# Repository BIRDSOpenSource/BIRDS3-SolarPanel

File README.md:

<div align="center">
  
</div>

# BIRDS3-SolarPanel
 Documentation for the Solar Panel Boards used in the BIRDS3 Satellite

## About the BIRDS3 Program:

The project was led by Kyushu Institute of Technology in Japan and involves students from Sri Lanka, Bhutan, Nepal and Japan.
Satellite Names: NepaliSat-1 (Nepal), Raavana-1 (Sri Lanka) and Ugiusu (Japan)

Stakeholders: Nepal Academy of Science and Technology (NAST) for Nepal, Arthur C Clarke Institute for Modern Technologies (ACCIMT) for Sri Lanka, and Kyushu Institute of Technology (Kyutech) for Japan.

Project duration: 2018-2020

CubeSat: 1U (10x10x10) cm3

Weight: 1.13kg

Launch Date: 17th April 2019

BIRDS-3 has 4 main missions in total; LoRa Demonstration Mission (LDM), Imaging Mission (CAM), Attitude Determination and Control Mission (ADCS) and Software Configurable Backplane Mission (BPB) 

## Organisation structure

## Features

## I like this project, can I help you?
You are welcome 🙂

* Give us a star ⭐
* Watch repository to be notified about updates 👀
* If you will find some errors, report them in Issues 🐞
* Try Birds designs on some real computer and let us know how it worked in Discussions. 💬
* We would greatly appreciate if you would also tell others about this ecosystem, it helps us to improve BIRDS Open Source. Thank you!

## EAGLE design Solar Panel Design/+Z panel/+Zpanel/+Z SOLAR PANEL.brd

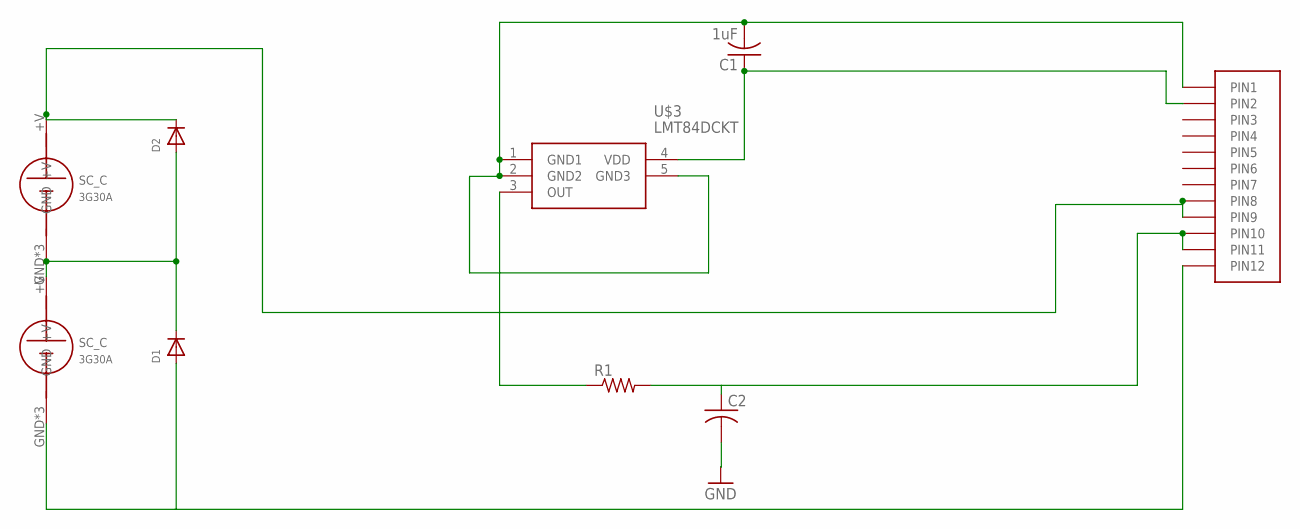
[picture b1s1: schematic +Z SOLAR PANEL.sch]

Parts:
C1: 1uF; C2012
C2: C-USC2012; C2012
D1, D2: DIODE_SOD-123FL; SOD-123FL
R1: R-US_R0402; R0402
U$1: HEADER12PIN
U$3: LMT84DCKT; SOT65P210X110-5N
U$4, U$5: SC_C

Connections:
+V: D2.C, U$1.P8 (PIN8), U$1.P9 (PIN9), U$4.+V
+VB: D1.C, D2.A, U$4.GND, U$4.GND1 (GND), U$4.GND2 (GND), U$5.+V
GND: C1.2, C2.2, D1.A, U$1.P1 (PIN1), U$1.P12 (PIN12), U$3.1 (GND1), U$3.2 (GND2), U$3.5 (GND3), U$5.GND, U$5.GND1 (GND), U$5.GND2 (GND)
unnamed: C1.1, U$1.P2 (PIN2), U$3.4 (VDD)
unnamed: R1.1, U$3.3 (OUT)
unnamed: C2.1, R1.2, U$1.P10 (PIN10), U$1.P11 (PIN11)

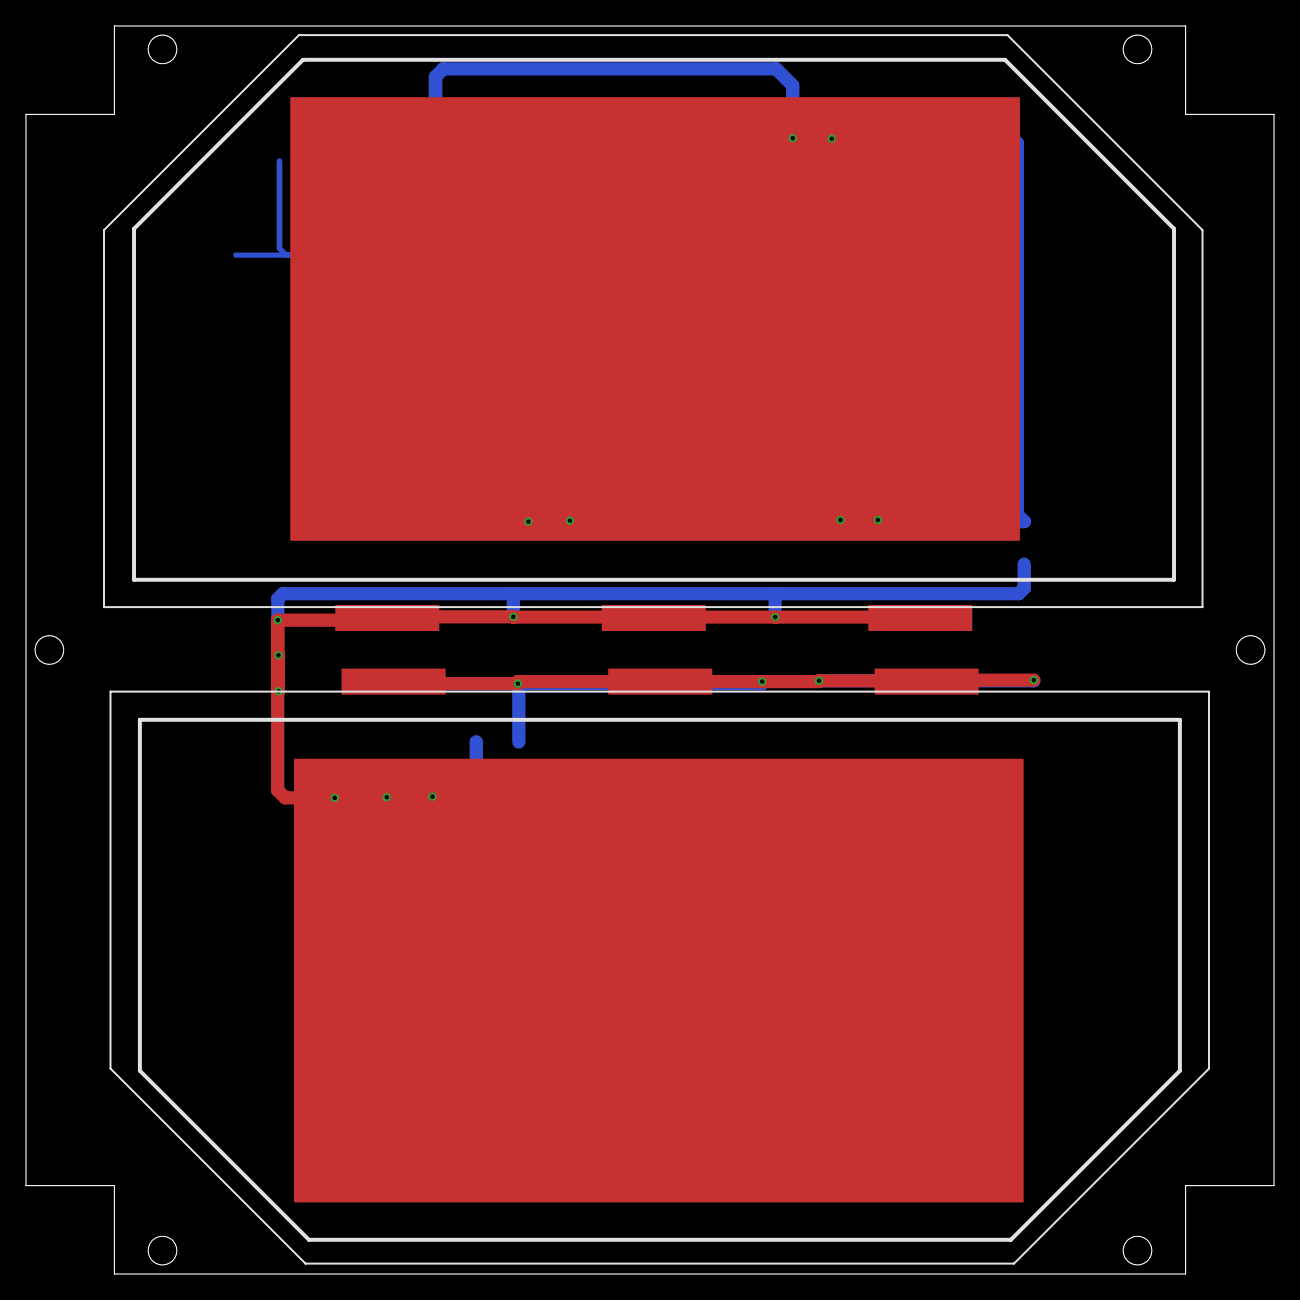
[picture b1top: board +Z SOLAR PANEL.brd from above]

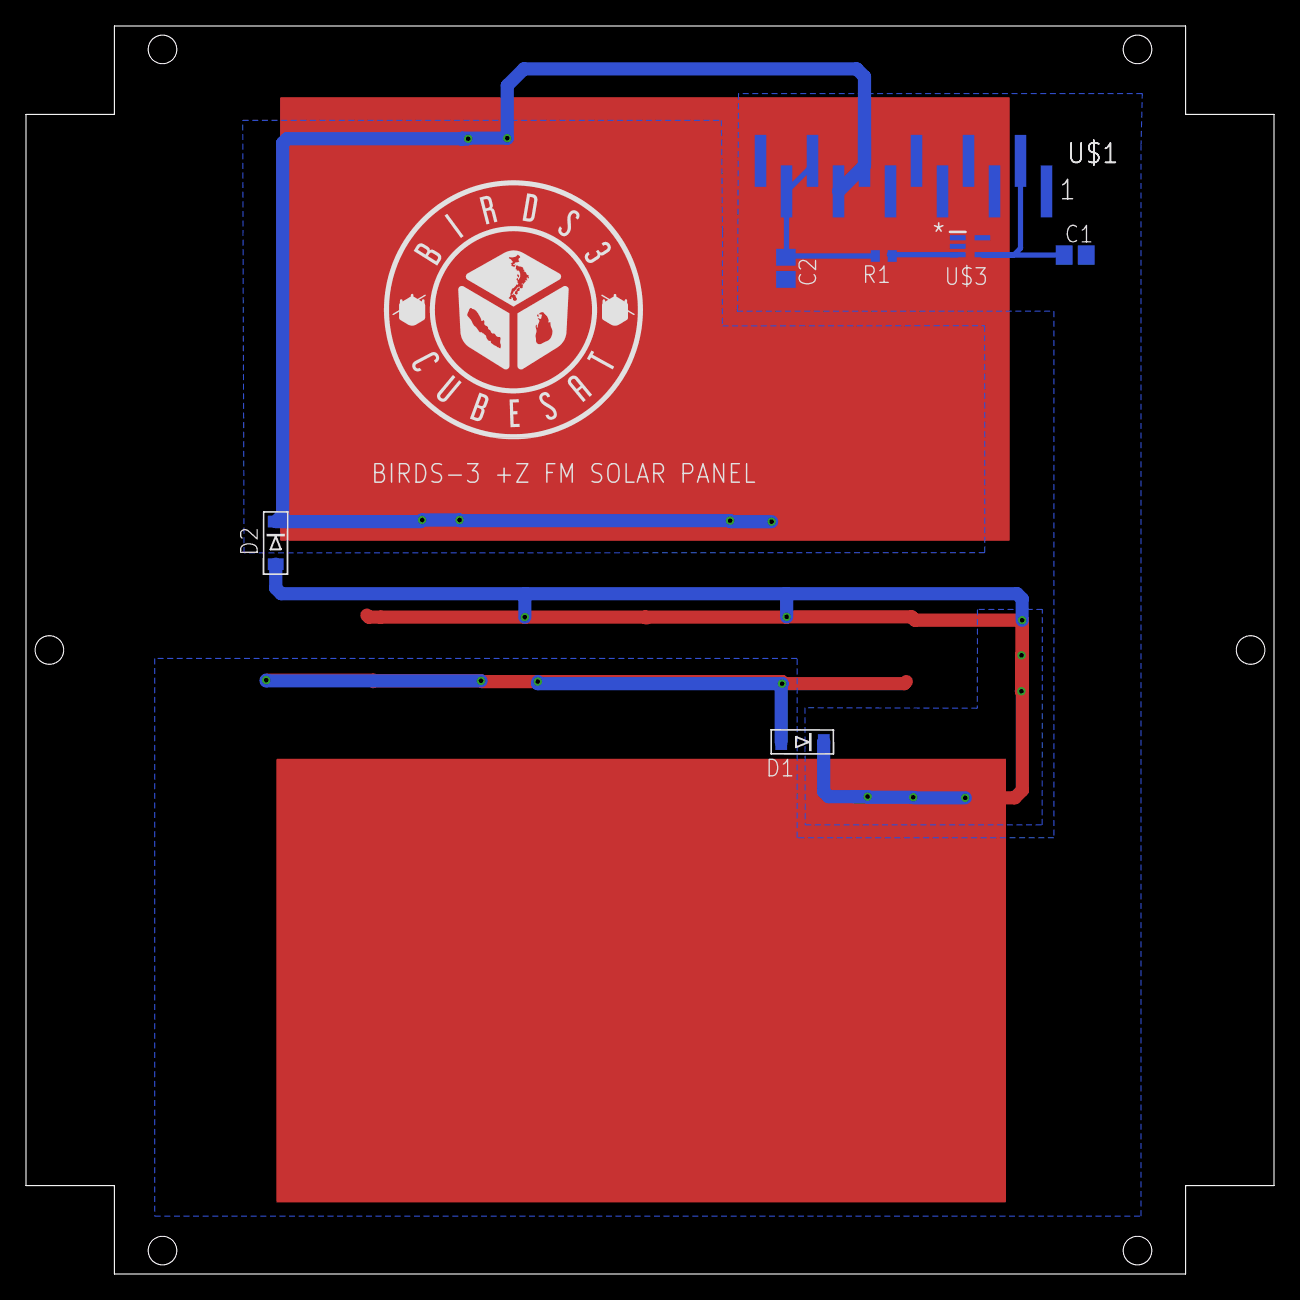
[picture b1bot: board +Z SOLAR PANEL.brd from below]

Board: 2 copper layers, 96.0 x 96.0 mm, 9 parts (5 on the bottom side), 6 nets.

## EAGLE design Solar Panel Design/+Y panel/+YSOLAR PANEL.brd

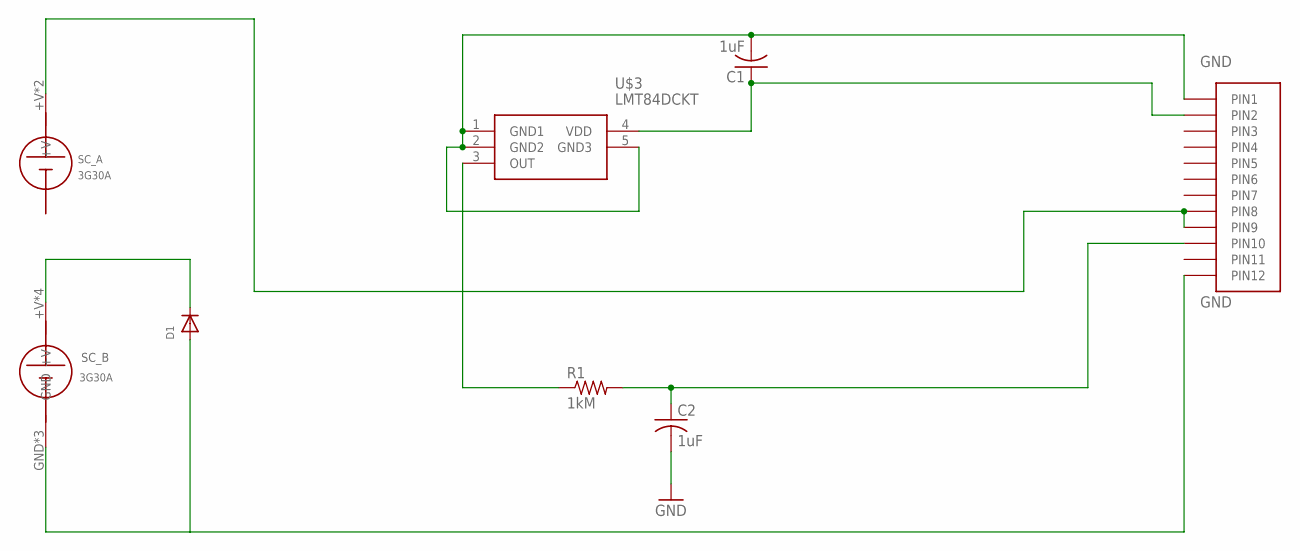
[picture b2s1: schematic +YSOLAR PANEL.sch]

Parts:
C1, C2: 1uF; C0805
D1: DIODE_SOD-123FL; SOD-123FL
R1: 1kM; R0402
SOLARCELL_A: SC_A
SOLARCELL_B: SC_B
U$1: HEADER12PIN
U$3: LMT84DCKT; SOT65P210X110-5N

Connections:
+V: SOLARCELL_A.+V, SOLARCELL_A.+V1, U$1.P8 (PIN8), U$1.P9 (PIN9)
+VB: D1.C, SOLARCELL_B.+V, SOLARCELL_B.+V2 (+V), SOLARCELL_B.+V3 (+V), SOLARCELL_B.+V4 (+V)
GND: C1.2, C2.2, D1.A, SOLARCELL_B.GND, SOLARCELL_B.GND1 (GND), SOLARCELL_B.GND2 (GND), U$1.P1 (PIN1), U$1.P12 (PIN12), U$3.1 (GND1), U$3.2 (GND2), U$3.5 (GND3)
unnamed: C1.1, U$1.P2 (PIN2), U$3.4 (VDD)
unnamed: R1.1, U$3.3 (OUT)
unnamed: C2.1, R1.2, U$1.P10 (PIN10)

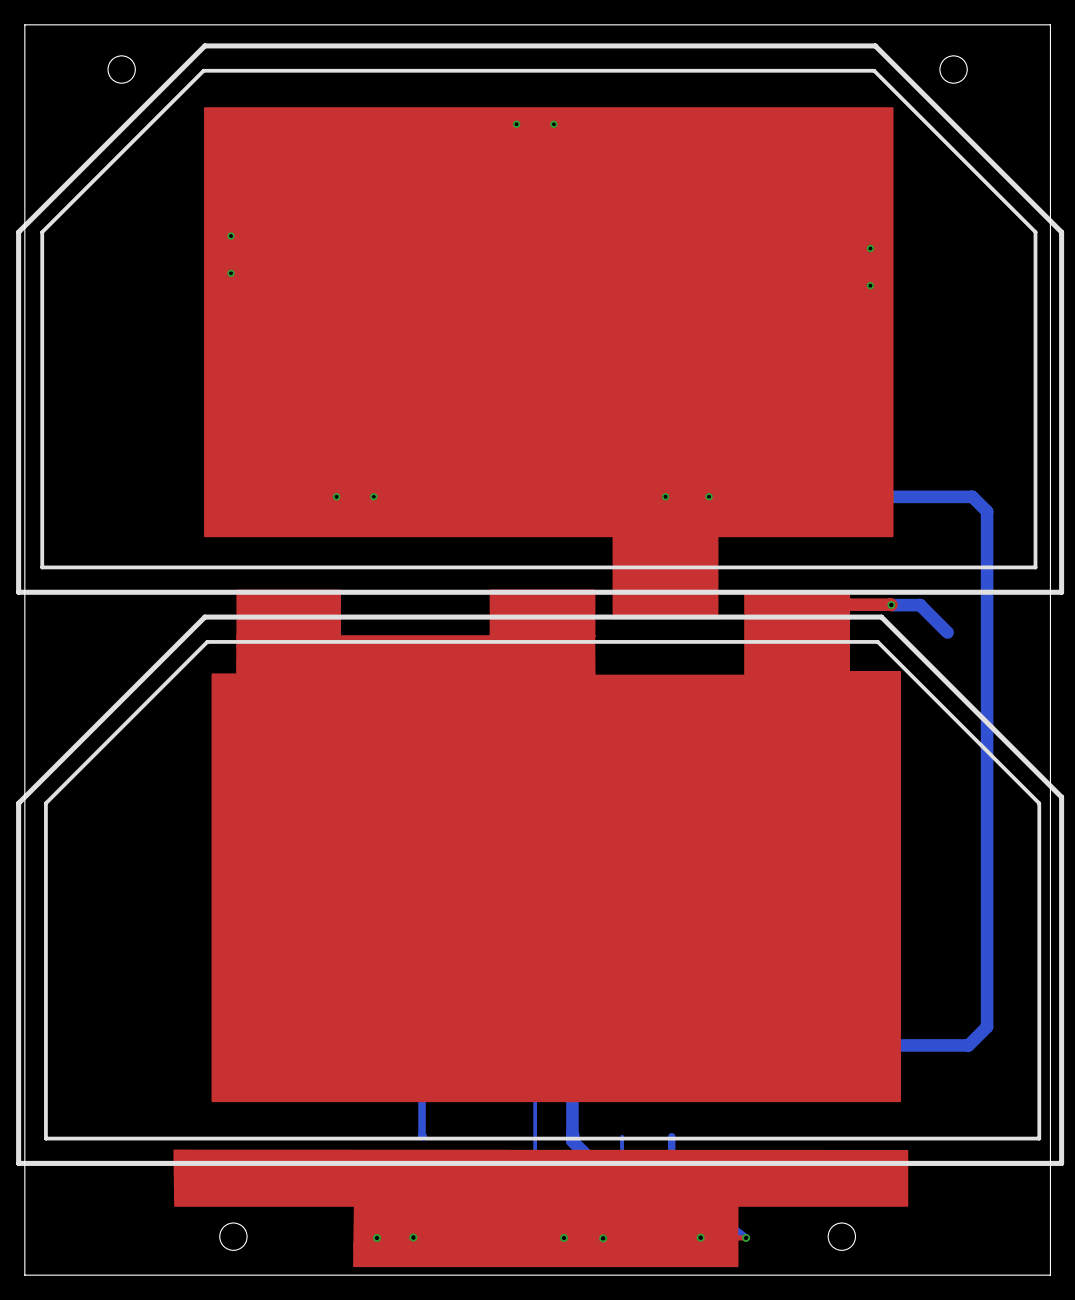
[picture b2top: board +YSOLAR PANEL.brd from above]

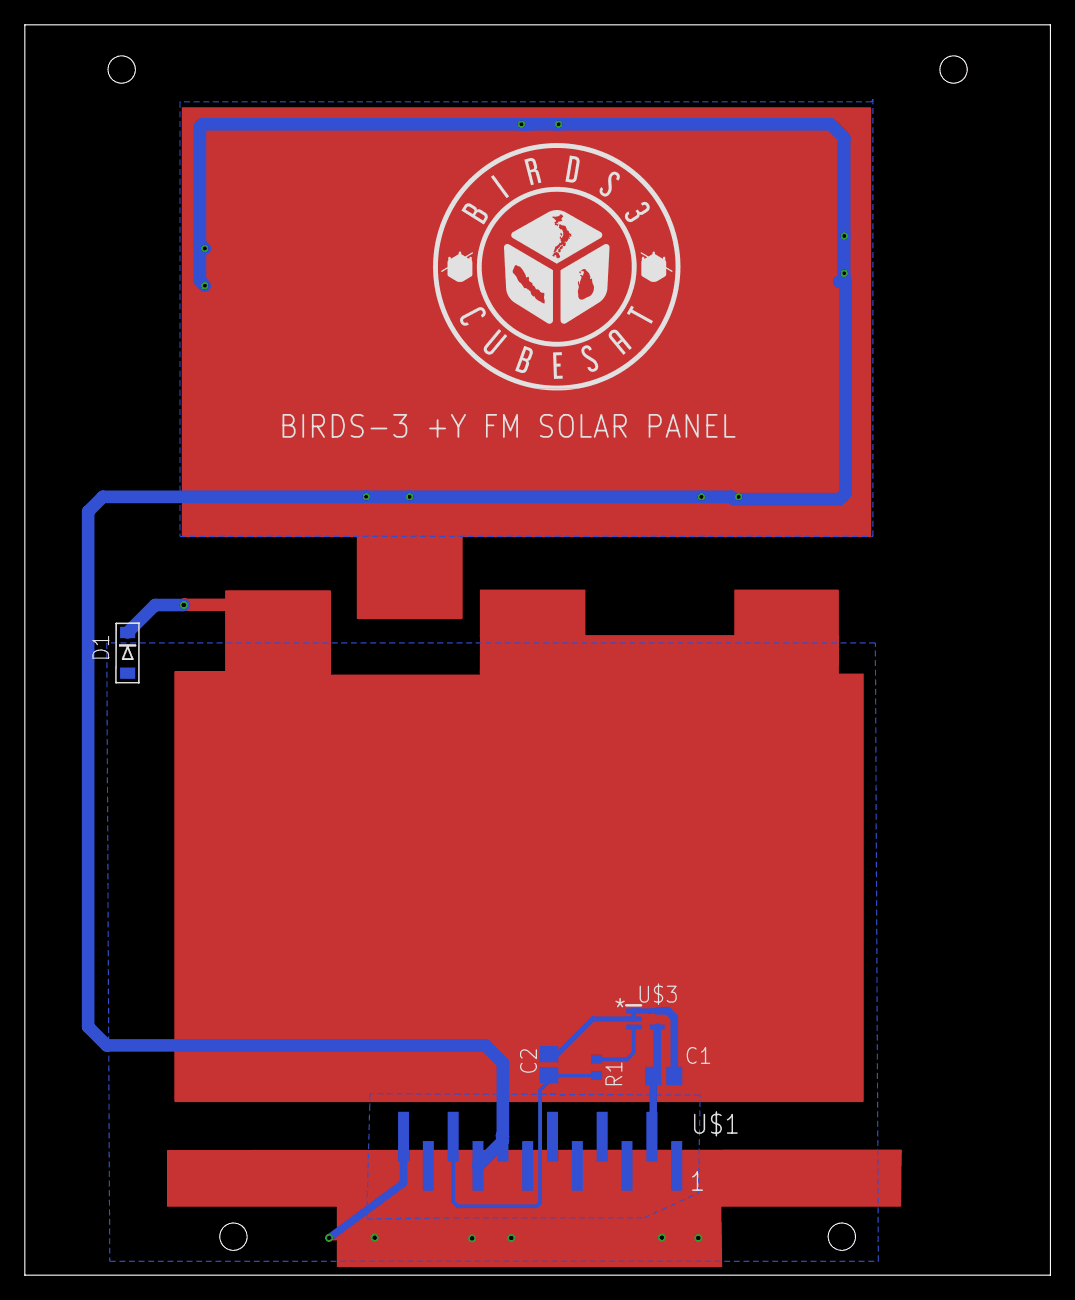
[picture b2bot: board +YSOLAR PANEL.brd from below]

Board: 2 copper layers, 82.6 x 100.7 mm, 8 parts (5 on the bottom side), 6 nets.

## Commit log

2021-10-20 Update LICENSE
